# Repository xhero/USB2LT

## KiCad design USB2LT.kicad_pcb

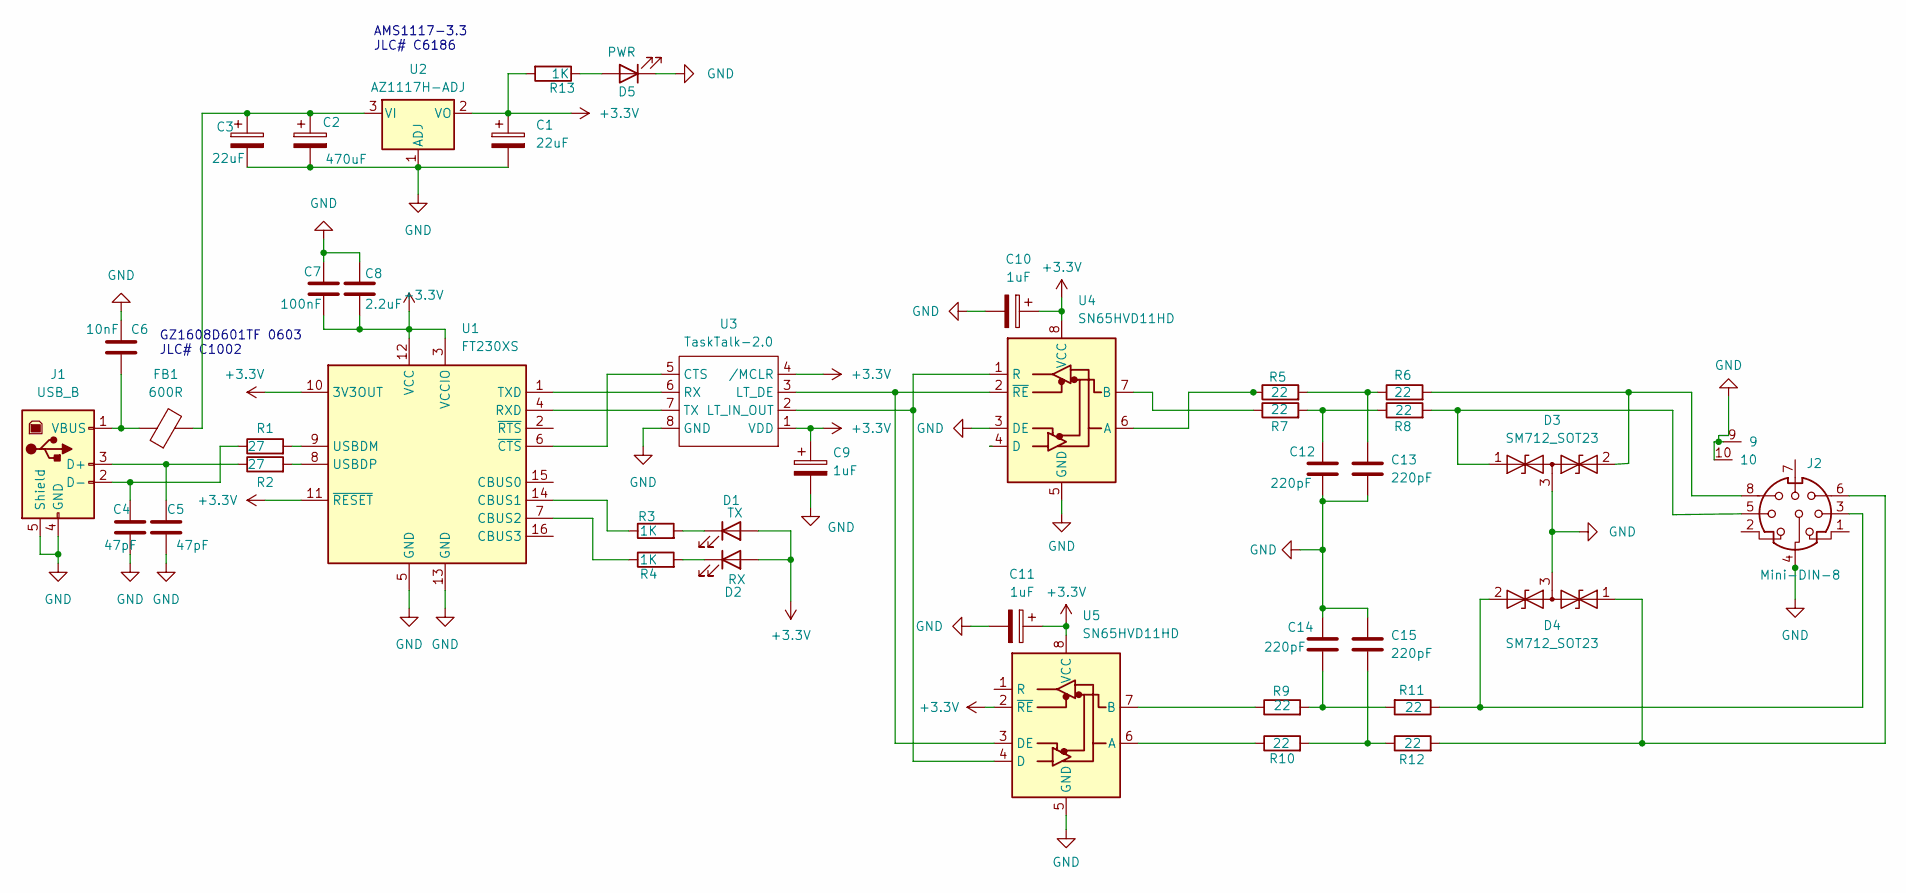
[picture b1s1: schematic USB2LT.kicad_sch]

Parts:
C1, C3: 22uF; C_0805_2012Metric
C2: 470uF; CP_Elec_6.3x7.7
C4, C5: 47pF; C_0805_2012Metric
C6: 10nF; C_0805_2012Metric
C7: 100nF; C_0805_2012Metric
C8: 2.2uF; C_0805_2012Metric
C9, C10, C11: 1uF; C_0805_2012Metric
C12, C13, C14, C15: 220pF; C_0805_2012Metric
D1: TX; LED_0805_2012Metric
D2: RX; LED_0805_2012Metric
D3, D4: SM712_SOT23; SOT-23
D5: PWR; LED_0805_2012Metric
FB1: 600R; R_0603_1608Metric
J1: USB_B; UJ2-BH-1-TH_CUD
J2: Mini-DIN-8; CONN_MDJ-004_ADM
R1, R2: 27; R_0805_2012Metric
R3, R4, R13: 1K; R_0805_2012Metric
R5, R6, R7, R8, R9, R10, R11, R12: 22; R_0805_2012Metric
U1: FT230XS; SSOP-16_3.9x4.9mm_P0.635mm
U2: AZ1117H-ADJ; SOT-223-3_TabPin2
U3: TaskTalk-2.0; SOIC-8_3.9x4.9mm_P1.27mm
U4, U5: SN65HVD11HD; SOIC-8_3.9x4.9mm_P1.27mm

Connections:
+3.3V: C1.1, C7.2, C8.2, C9.1, C10.1, C11.1, D1.2 (A), D2.2 (A), R13.2, U1.3 (VCCIO), U1.10 (3V3OUT), U1.11 (~RESET), U1.12 (VCC), U2.2 (VO), U3.1 (VDD), U3.4 (/MCLR), U4.8 (VCC), U5.2 (~RE), U5.8 (VCC)
GND: C1.2, C2.2, C3.2, C4.2, C5.2, C6.1, C7.1, C8.1, C9.2, C10.2, C11.2, C12.2, C13.2, C14.1, C15.1, D3.3 (common), D4.3 (common), D5.1 (K), J1.4 (GND), J1.5 (Shield), J2.4, J2.9, J2.10, U1.5 (GND), U1.13 (GND), U2.1 (ADJ), U3.8 (GND), U4.3 (DE), U4.5 (GND), U5.5 (GND)
unnamed: C12.1, R7.2, R8.1
unnamed: C13.1, R5.2, R6.1
unnamed: C14.2, R9.2, R11.2
unnamed: C15.2, R10.2, R12.1
unnamed: D1.1 (K), R3.2
unnamed: D2.1 (K), R4.2
unnamed: D3.1 (A1), J2.5, R8.2
unnamed: D3.2 (A2), J2.8, R6.2
unnamed: D4.1 (A1), J2.6, R12.2
unnamed: D4.2 (A2), J2.3, R11.1
unnamed: D5.2 (A), R13.1
unnamed: C5.1, J1.3 (D+), R2.1
unnamed: C4.1, J1.2 (D-), R1.1
unnamed: C6.2, FB1.1, J1.1 (VBUS)
unnamed: R3.1, U1.14 (CBUS1)
unnamed: R4.1, U1.7 (CBUS2)
unnamed: U1.4 (RXD), U3.7 (TX)
unnamed: U1.1 (TXD), U3.6 (RX)
unnamed: R1.2, U1.9 (USBDM)
unnamed: R2.2, U1.8 (USBDP)
unnamed: U1.6 (~CTS), U3.5 (CTS)
unnamed: C2.1, C3.1, FB1.2, U2.3 (VI)
unnamed: U3.3 (LT_DE), U4.2 (~RE), U5.3 (DE)
unnamed: U3.2 (LT_IN_OUT), U4.1 (R), U5.4 (D)
unnamed: R5.1, U4.6 (A)
unnamed: R7.1, U4.7 (B)
unnamed: R10.1, U5.6 (A)
unnamed: R9.1, U5.7 (B)

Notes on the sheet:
GZ1608D601TF 0603 JLC# C1002
AMS1117-3.3 JLC# C6186

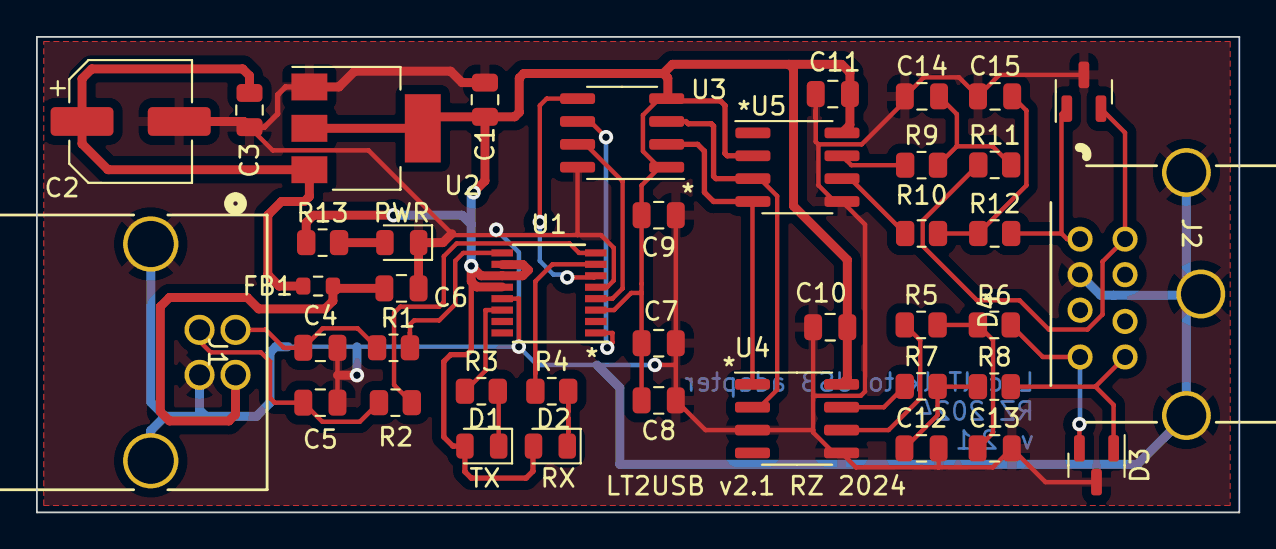
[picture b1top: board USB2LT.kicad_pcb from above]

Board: 2 copper layers, 66.8 x 26.4 mm, 41 parts (0 on the bottom side), 30 nets.

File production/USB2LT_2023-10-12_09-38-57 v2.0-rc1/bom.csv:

"Designator","Footprint","Quantity","Value","LCSC Part #"
"C1, C3",805,2,"22uF","C45783"
"C10, C11, C9",805,3,"1uF","C28323"
"C12, C13, C14, C15",805,4,"220pF","C107145"
"C2","CP_Elec_6.3x7.7",1,"470uF",
"C4, C5",805,2,"47pF","C14857"
"C6",805,1,"10nF","C1710"
"C7",805,1,"100nF","C49678"
"C8",805,1,"2.2uF","C377773"
"D1, D2",805,2,"LED","C2293"
"D3, D4","SOT-23",2,"SM712_SOT23","C5451662"
"FB1",402,1,"600R","C19136"
"J1","USB_B_TE_5787834_Vertical",1,"USB_B","C305923"
"J2","CONN_MDJ-004_ADM",1,"Mini-DIN-8",
"R1, R2",805,2,27,"C17561"
"R10, R11, R12, R5, R6, R7, R8, R9",805,8,25,"C17561"
"R3, R4",805,2,"1K","C17513"
"U1","SSOP-16_3.9x4.9mm_P0.635mm",1,"FT230XS","C69082"
"U2","SOT-223-3_TabPin2",1,"AZ1117H-ADJ","C108492"
"U3","SOIC-8_3.9x4.9mm_P1.27mm",1,"TaskTalk-2.0",
"U4, U5","SOIC-8_3.9x4.9mm_P1.27mm",2,"SN65HVD11HD","C68886"

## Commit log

2023-11-12 Add usb2lt stuff
2023-11-12 New version
2024-01-20 Fix short
2024-02-11 v2.1
2024-02-11 Add production files
